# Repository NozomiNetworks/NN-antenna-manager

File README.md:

# NN-antenna-manager

Open source hardware + firmware for a custom antenna manager (RF selector) for SDR cards.

The board lets an SDR receiver/transceiver share a single RF port while switching between up to
**8 antennas** through a 50 Ω **SP8T RF switch**, plus a **tri-state** (all ports disconnected)
mode. Antenna selection can be changed:

- locally, with **2 buttons + an OLED display**;
- over **USB / TTL serial / BLE** with a text CLI;
- from a **BLE GATT client** (custom characteristics for channel, antenna Hz ranges, RF enable);
- from a **WiFi web portal** (status, channel selection, antenna configuration).

The selector state is persisted and re-applied immediately at boot, before any radio is enabled.
For SDR capture sessions, the ESP32's own WiFi/Bluetooth stage can be disabled entirely
(persisted until re-enabled) so the device does not emit any RF itself.

## Repository structure

```
hardware/
  kicad_project/   KiCad 8+ schematic and PCB (NN-antenna-manager.kicad_pro)
  fabrication/     BOM.xlsx, CPL.xlsx (pick & place), gerber.zip — ready for manufacturing
software/          Arduino IDE sketch for the ESP32-C3-WROOM-02 (see software/README.md)
LICENSES/          CERN-OHL-P-2.0.txt, Apache-2.0.txt
```

## Hardware

KiCad project with full fabrication outputs. Main components:

| Ref | Part | Role |
|-----|------|------|
| U1 | ESP32-C3-WROOM-02 | WiFi 2.4 GHz + BLE 5 module (RISC-V), runs the firmware |
| IC1 | PE42482A-X (pSemi) | SP8T absorptive 50 Ω RF switch, QFN-24 |
| U3 | AP2112K-3.3 | 3.3 V / 600 mA LDO regulator |
| U2 | USBLC6-2SC6 | ESD protection on the USB data lines |
| D1–D3 | PESD5V0L1ULD + LED | ESD protection, status LED |
| J2–J10 | SMA edge-mount (Amphenol 132289) | 8 antenna ports + 1 common port (to the SDR) |
| J1 | USB-C receptacle | Power + native USB serial (CLI) |
| J11 | 1x04 pin socket | I2C header for the SSD1306 128x64 OLED |
| J12 | 1x03 pin header | TTL UART (Serial1 CLI) |
| SW1–SW4 | B3U-1000P push buttons | NEXT / ENTER menu navigation |

The default pin mapping (buttons, I2C, UART, selector bits S0–S3) is defined in
`software/Config.h` and documented in `software/README.md`.

### Selector logic

```
SELECT #1..#7  ->  S3=0, S2:S0 = 1..7 (binary)
TRI-STATE      ->  S3=1, S2:S0 = 0
```

## Software

The `software/` folder is an Arduino IDE sketch (open the folder directly; the `.ino` plus all
`.h/.cpp` files compile together). Features:

- **Local UI** — boot logo, status bar (WiFi signal, BLE, channel, antenna Hz range), menu with
  channel selection, tri-state and RF enable/disable; display auto-off after 30 s.
- **CLI** (same command set on TTL serial, USB CDC and BLE Nordic-UART):
  `help`, `status`, `select <1-7>`, `tristate`, `rf on|off|toggle`, `name`, `wifi`, `ant`,
  `save`, `reboot`.
- **BLE GATT** — Device Information Service (0x180A), custom service with selected channel,
  active antenna Hz range, "Enable RF" boolean, and per-antenna Hz ranges (read/write).
- **Web portal** — `/` status, `/antennas`, `/channel`, `/wifi` (setup AP fallback if no SSID is
  configured), `/api/status` (JSON).
- **Persistence** — selector and RF state in an external I2C EEPROM (24LCxx, or NVS emulation via
  `USE_EXTERNAL_EEPROM 0`); device name, WiFi credentials and per-antenna Hz ranges in SPIFFS
  (`/config.json`).

Required libraries, wiring tables, build options and flashing instructions (including the SPIFFS
boot logo) are detailed in **[software/README.md](software/README.md)**.

## Getting started

1. **Board**: order the PCB using `hardware/fabrication/gerber.zip` with `BOM.xlsx` and
   `CPL.xlsx`, or open `hardware/kicad_project/NN-antenna-manager.kicad_pro` to modify/re-export.
2. **Firmware**: open `software/` in the Arduino IDE, select an **ESP32C3 Dev Module** board with
   **USB CDC On Boot: Enabled**, install the libraries listed in `software/README.md`, and flash.
3. **Use**: select the antenna from the OLED menu, the web portal, a BLE app or the serial CLI;
   set each antenna's known Hz range so the `/channel` page can suggest the right one.

## License

- `hardware/` — [CERN Open Hardware Licence Version 2 - Permissive](LICENSES/CERN-OHL-P-2.0.txt)
- `software/` — [Apache License 2.0](LICENSES/Apache-2.0.txt)

See [LICENSE](LICENSE) for details.

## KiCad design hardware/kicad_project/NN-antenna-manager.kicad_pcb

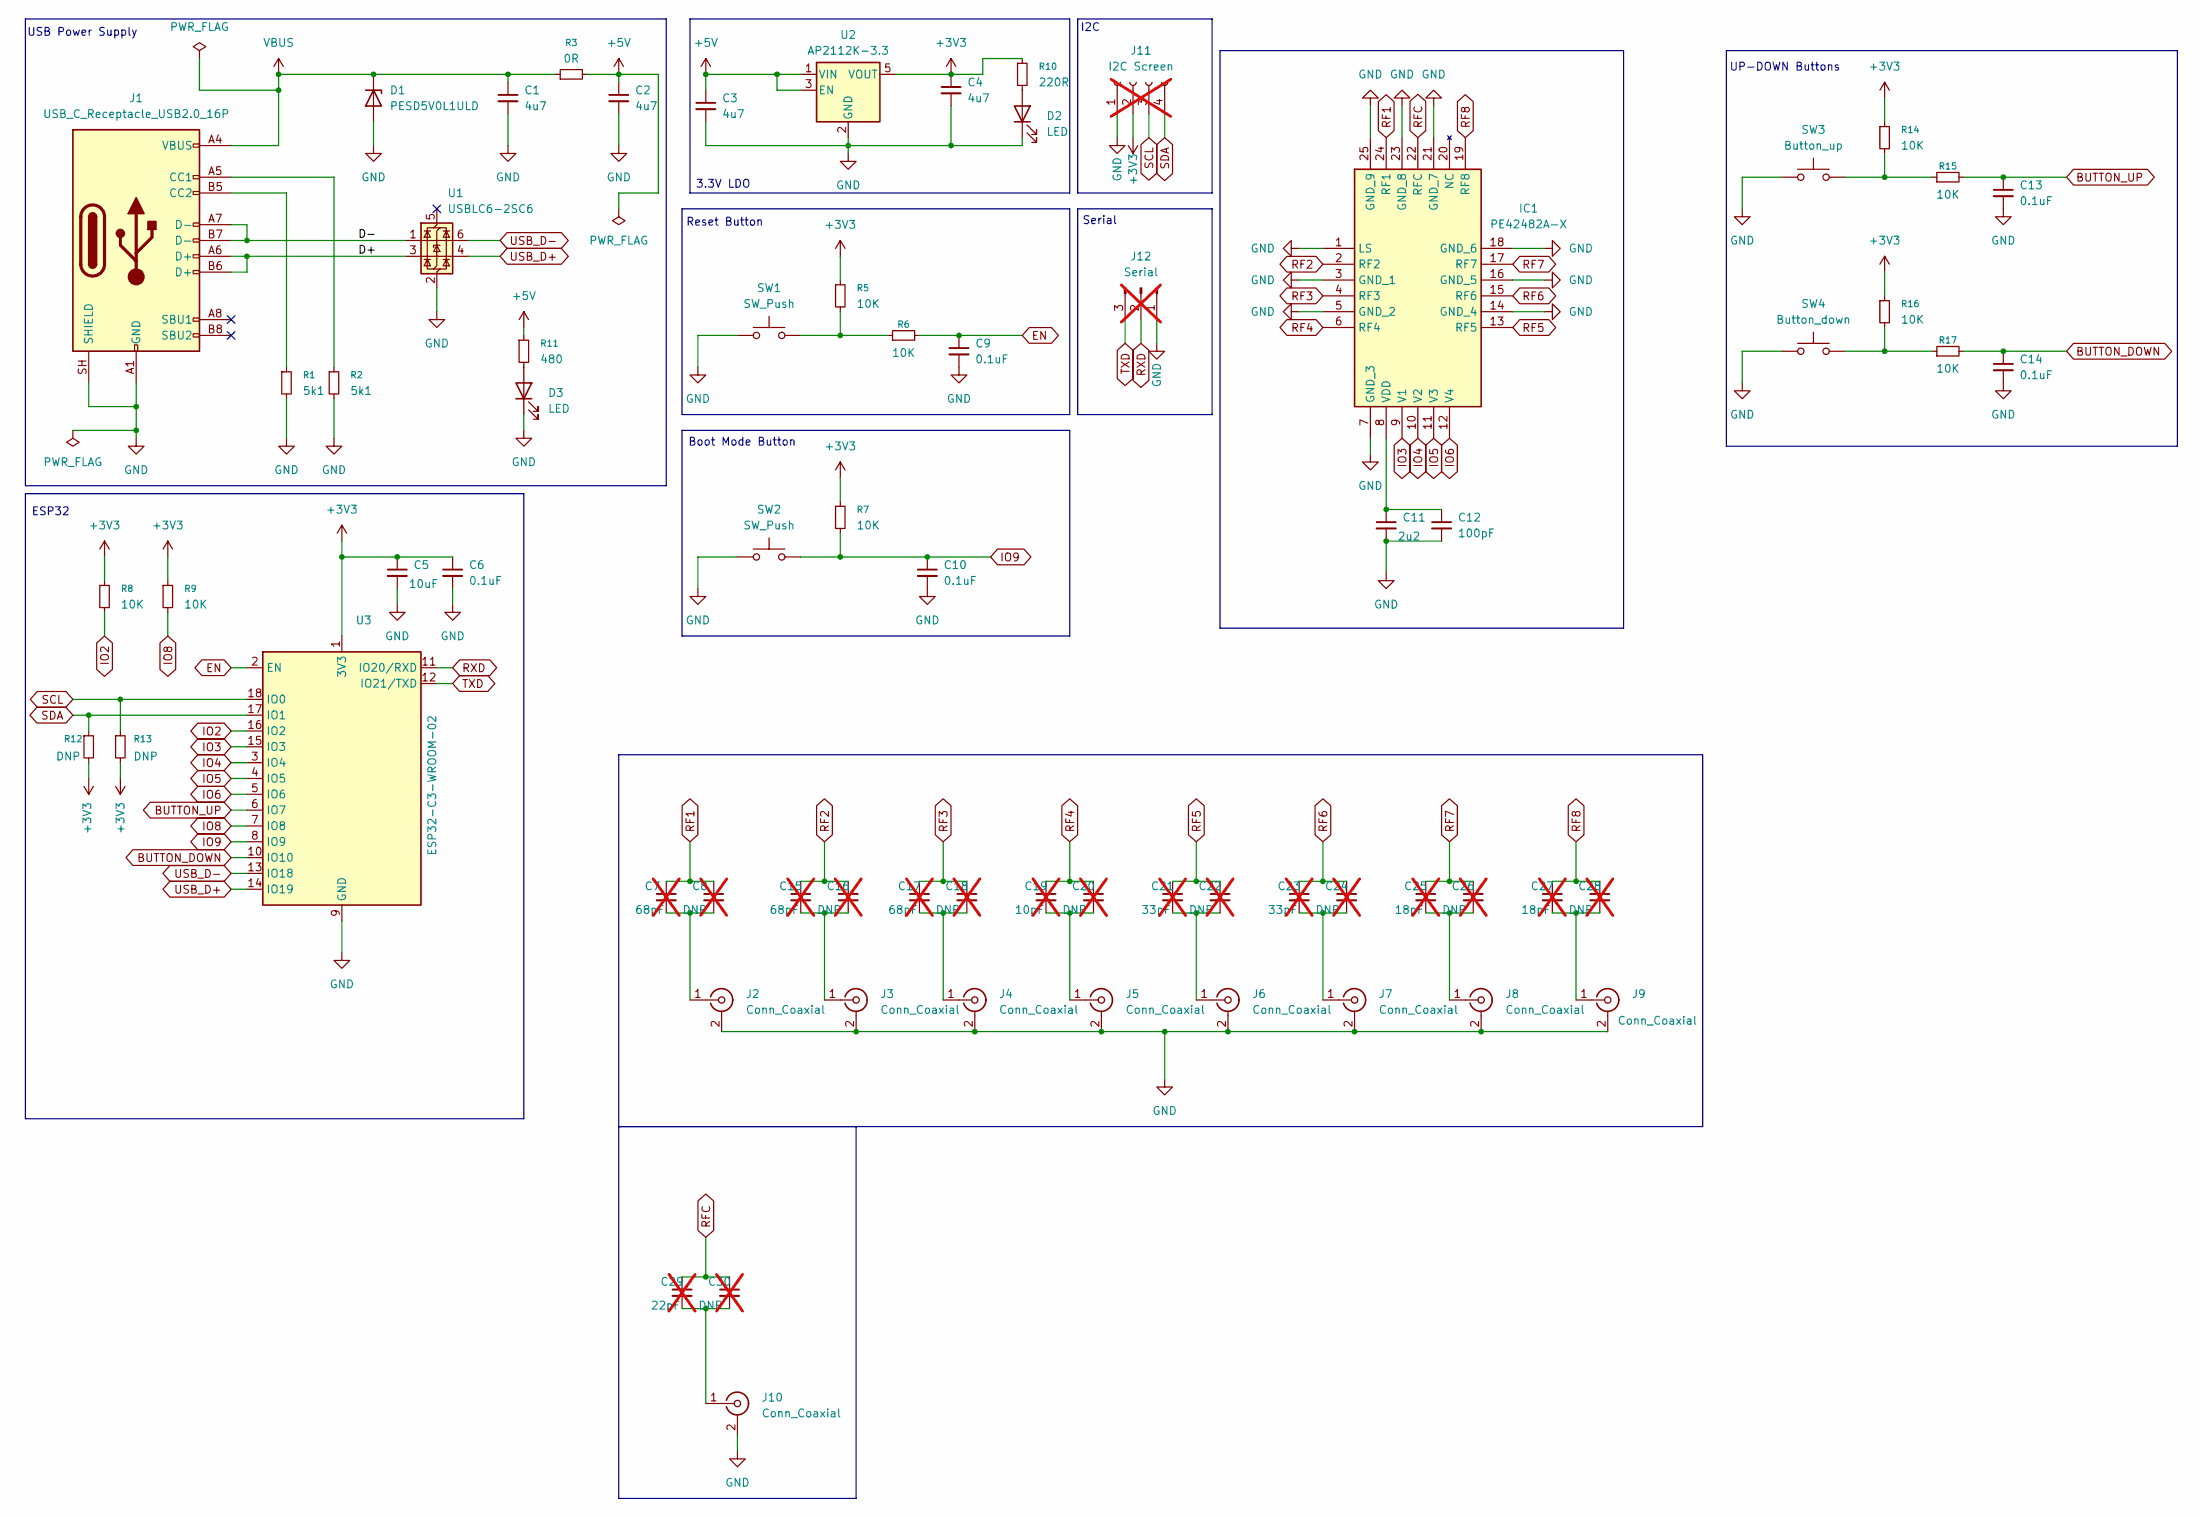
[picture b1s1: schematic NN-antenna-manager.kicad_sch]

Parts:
C1, C2, C3, C4: 4u7; C_0603_1608Metric_Pad1.08x0.95mm_HandSolder; JLCPCB Part# C19666
C5: 10uF; C_0805_2012Metric_Pad1.18x1.45mm_HandSolder; JLCPCB Part# C1713
C6, C9, C10, C13, C14: 0.1uF; C_0603_1608Metric_Pad1.08x0.95mm_HandSolder; JLCPCB Part# C66501
C7, C15, C17: 68pF; C_0402_1005Metric_Pad0.74x0.62mm_HandSolder; JLCPCB Part# DNP; not fitted
C8, C16, C18, C20, C22, C24, C26, C28, C30: DNP; C_0402_1005Metric_Pad0.74x0.62mm_HandSolder; JLCPCB Part# DNP; not fitted
C11: 2u2; C_0805_2012Metric_Pad1.18x1.45mm_HandSolder; JLCPCB Part# C28234
C12: 100pF; C_0603_1608Metric_Pad1.08x0.95mm_HandSolder; JLCPCB Part# C1853160
C19: 10pF; C_0402_1005Metric_Pad0.74x0.62mm_HandSolder; JLCPCB Part# DNP; not fitted
C21, C23: 33pF; C_0402_1005Metric_Pad0.74x0.62mm_HandSolder; JLCPCB Part# DNP; not fitted
C25, C27: 18pF; C_0402_1005Metric_Pad0.74x0.62mm_HandSolder; JLCPCB Part# DNP; not fitted
C29: 22pF; C_0402_1005Metric_Pad0.74x0.62mm_HandSolder; JLCPCB Part# DNP; not fitted
D1: PESD5V0L1ULD; D_SOD-882; JLCPCB Part# C3001948
D2, D3: LED; LED_1206_3216Metric_Pad1.42x1.75mm_HandSolder; JLCPCB Part# C965827
IC1: PE42482A-X; QFN50P400X400X90-25N; Manufacturer_Part_Number PE42482A-X; Mouser Part Number 81-PE42482A-X
J1: USB_C_Receptacle_USB2.0_16P; USB_C_Receptacle_G-Switch_GT-USB-7010ASV; JLCPCB Part# C2988369
J2, J3, J4, J5, J6, J7, J8, J9, J10: Conn_Coaxial; SMA_Amphenol_132289_EdgeMount; JLCPCB Part# C3172723
J11: I2C Screen; PinSocket_1x04_P2.54mm_Vertical; JLCPCB Part# DNP; not fitted
J12: Serial; PinHeader_1x03_P2.54mm_Vertical; JLCPCB Part# DNP; not fitted
R1, R2: 5k1; R_0603_1608Metric_Pad0.98x0.95mm_HandSolder; JLCPCB Part# C23186
R3: 0R; R_0805_2012Metric_Pad1.20x1.40mm_HandSolder; JLCPCB Part# C17477
R5, R6, R7, R8, R9, R14, R15, R16, R17: 10K; R_0603_1608Metric_Pad0.98x0.95mm_HandSolder; JLCPCB Part# C25804
R10: 220R; R_0603_1608Metric_Pad0.98x0.95mm_HandSolder; JLCPCB Part# C22962
R11: 480; R_0603_1608Metric_Pad0.98x0.95mm_HandSolder; JLCPCB Part# C23179
R12, R13: DNP; R_0603_1608Metric_Pad0.98x0.95mm_HandSolder; JLCPCB Part# DNP
SW1, SW2: SW_Push; SW_SPST_B3U-1000P; JLCPCB Part# C231329
SW3: Button_up; SW_SPST_B3U-1000P; JLCPCB Part# C231329
SW4: Button_down; SW_SPST_B3U-1000P; JLCPCB Part# C231329
U1: USBLC6-2SC6; SOT-23-6; JLCPCB Part# C2687116
U2: AP2112K-3.3; SOT-23-5_HandSoldering; JLCPCB Part# C51118
U3: ESP32-C3-WROOM-02; JLCPCB Part# C2934560

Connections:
+3V3: C4.1, C5.1, C6.1, J11.2, R5.1, R7.1, R8.1, R9.1, R10.1, R12.2, R13.2, R14.1, R16.1, U2.5 (VOUT), U3.1 (3V3)
+5V: C2.1, C3.1, R3.2, R11.1, U2.1 (VIN), U2.3 (EN)
/D+: J1.A6 (D+), J1.B6 (D+), U1.3 (I/O2)
/D-: J1.A7 (D-), J1.B7 (D-), U1.1 (I/O1)
BUTTON_DOWN: C14.1, R17.2, U3.10 (IO10)
BUTTON_UP: C13.1, R15.2, U3.6 (IO7)
EN: C9.1, R6.2, U3.2 (EN)
GND: C1.2, C2.2, C3.2, C4.2, C5.2, C6.2, C9.2, C10.2, C11.2, C12.2, C13.2, C14.2, D1.2 (A), D2.1 (K), D3.1 (K), IC1.1 (LS), IC1.3 (GND_1), IC1.5 (GND_2), IC1.7 (GND_3), IC1.14 (GND_4), IC1.16 (GND_5), IC1.18 (GND_6), IC1.21 (GND_7), IC1.23 (GND_8), IC1.25 (GND_9), J1.A1 (GND), J1.A12 (GND), J1.B1 (GND), J1.B12 (GND), J1.SH (SHIELD), J2.2 (Ext), J3.2 (Ext), J4.2 (Ext), J5.2 (Ext), J6.2 (Ext), J7.2 (Ext), J8.2 (Ext), J9.2 (Ext), J10.2 (Ext), J11.1, J12.1, R1.2, R2.2, SW1.1, SW2.1, SW3.1, SW4.1, U1.2 (GND), U2.2 (GND), U3.9 (GND), U3.19 (GND)
IO2: R8.2, U3.16 (IO2)
IO3: IC1.9 (V1), U3.15 (IO3)
IO4: IC1.10 (V2), U3.3 (IO4)
IO5: IC1.11 (V3), U3.4 (IO5)
IO6: IC1.12 (V4), U3.5 (IO6)
IO8: R9.2, U3.7 (IO8)
IO9: C10.1, R7.2, SW2.2, U3.8 (IO9)
unnamed: D2.2 (A), R10.2
unnamed: D3.2 (A), R11.2
unnamed: C11.1, C12.1, IC1.8 (VDD)
unnamed: J1.A5 (CC1), R2.1
unnamed: J1.B5 (CC2), R1.1
unnamed: C7.2, C8.2, J2.1 (In)
unnamed: C15.2, C16.2, J3.1 (In)
unnamed: C17.2, C18.2, J4.1 (In)
unnamed: C19.2, C20.2, J5.1 (In)
unnamed: C21.2, C22.2, J6.1 (In)
unnamed: C23.2, C24.2, J7.1 (In)
unnamed: C25.2, C26.2, J8.1 (In)
unnamed: C27.2, C28.2, J9.1 (In)
unnamed: C29.2, C30.2, J10.1 (In)
unnamed: R5.2, R6.1, SW1.2
unnamed: R14.2, R15.1, SW3.2
unnamed: R16.2, R17.1, SW4.2
RF1: C7.1, C8.1, IC1.24 (RF1)
RF2: C15.1, C16.1, IC1.2 (RF2)
RF3: C17.1, C18.1, IC1.4 (RF3)
RF4: C19.1, C20.1, IC1.6 (RF4)
RF5: C21.1, C22.1, IC1.13 (RF5)
RF6: C23.1, C24.1, IC1.15 (RF6)
RF7: C25.1, C26.1, IC1.17 (RF7)
RF8: C27.1, C28.1, IC1.19 (RF8)
RFC: C29.1, C30.1, IC1.22 (RFC)
RXD: J12.2, U3.11 (IO20/RXD)
SCL: J11.3, R13.1, U3.18 (IO0)
SDA: J11.4, R12.1, U3.17 (IO1)
TXD: J12.3, U3.12 (IO21/TXD)
USB_D+: U1.4 (I/O2), U3.14 (IO19)
USB_D-: U1.6 (I/O1), U3.13 (IO18)
VBUS: C1.1, D1.1 (K), J1.A4 (VBUS), J1.A9 (VBUS), J1.B4 (VBUS), J1.B9 (VBUS), R3.1

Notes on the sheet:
ESP32
USB Power Supply
I2C
Boot Mode Button
3.3V LDO
Serial
Reset Button
UP-DOWN Buttons

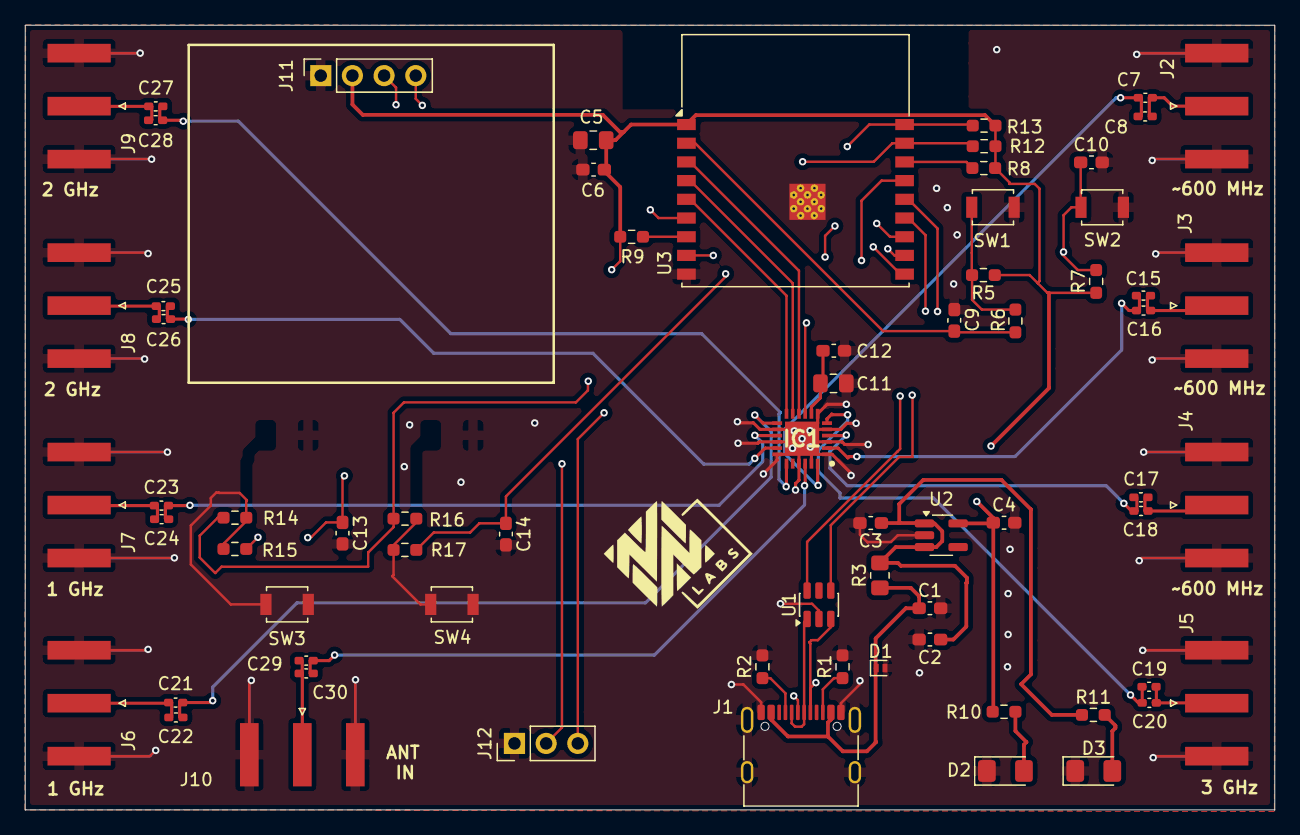
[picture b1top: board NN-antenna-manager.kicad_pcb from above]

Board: 4 copper layers, 100.2 x 62.9 mm, 69 parts (0 on the bottom side), 48 nets.

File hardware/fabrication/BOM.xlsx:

Comment | Designator | Footprint | JLCPCB Part #（optional）
4u7 | C1,C2,C3,C4 | Capacitor_SMD:C_0603_1608Metric_Pad1.08x0.95mm_HandSolder | C19666
10uF | C5 | Capacitor_SMD:C_0805_2012Metric_Pad1.18x1.45mm_HandSolder | C1713
0.1uF | C6,C9,C10,C13,C14 | Capacitor_SMD:C_0603_1608Metric_Pad1.08x0.95mm_HandSolder | C66501
2u2 | C11 | Capacitor_SMD:C_0805_2012Metric_Pad1.18x1.45mm_HandSolder | C28234
100pF | C12 | Capacitor_SMD:C_0603_1608Metric_Pad1.08x0.95mm_HandSolder | C1853160
PESD5V0L1ULD | D1 | Diode_SMD:D_SOD-882 | C3001948
LED | D2,D3 | LED_SMD:LED_1206_3216Metric_Pad1.42x1.75mm_HandSolder | C965827
PE42482A-X | IC1 | PE42482A-X:QFN50P400X400X90-25N | C5121458
USB_C_Receptacle_USB2.0_16P | J1 | Connector_USB:USB_C_Receptacle_G-Switch_GT-USB-7010ASV | C2988369
Conn_Coaxial | J2,J3,J4,J5,J6,J7,J8,J9,J10 | Connector_Coaxial:SMA_Amphenol_132289_EdgeMount | C3172723
5k1 | R1,R2 | Resistor_SMD:R_0603_1608Metric_Pad0.98x0.95mm_HandSolder | C23186
0R | R3 | Resistor_SMD:R_0805_2012Metric_Pad1.20x1.40mm_HandSolder | C17477
10K | R5,R6,R7,R8,R9,R14,R15,R16,R17 | Resistor_SMD:R_0603_1608Metric_Pad0.98x0.95mm_HandSolder | C25804
220R | R10 | Resistor_SMD:R_0603_1608Metric_Pad0.98x0.95mm_HandSolder | C22962
480R | R11 | Resistor_SMD:R_0603_1608Metric_Pad0.98x0.95mm_HandSolder | C23179
SW_Push | SW1,SW2 | Button_Switch_SMD:SW_SPST_B3U-1000P | C231329
Button_up | SW3 | Button_Switch_SMD:SW_SPST_B3U-1000P | C231329
Button_down | SW4 | Button_Switch_SMD:SW_SPST_B3U-1000P | C231329
USBLC6-2SC6 | U1 | Package_TO_SOT_SMD:SOT-23-6 | C2687116
AP2112K-3.3 | U2 | Package_TO_SOT_SMD:SOT-23-5_HandSoldering | C51118
ESP32-C3-WROOM-02 | U3 | RF_Module:ESP32-C3-WROOM-02 | C2934560
